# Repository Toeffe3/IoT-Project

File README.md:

# IoT-Project
University Project designing an IoT system

# Setup IDE
### Microchip studio

Following architectures are required:

_Run the `as-installer-*.exe` and select `AVR` and `UC3` (click **Repair**, if you have MCS installed but missing any of the architectures)_

Following extensions are optional:
* `ClangFormat`
* `Git Source Controle Provider`

---

**Integrate with Git trickery**

Open the project the first time by double-clicking the `IoT-Project.atsln` file, if no projects apperes in the Solution Explorer, you have to manually add them by left-clicking the Solution -> Add -> Existing Project -> Navigate to either one of the `*.ccproj` files, and repeat for the other.

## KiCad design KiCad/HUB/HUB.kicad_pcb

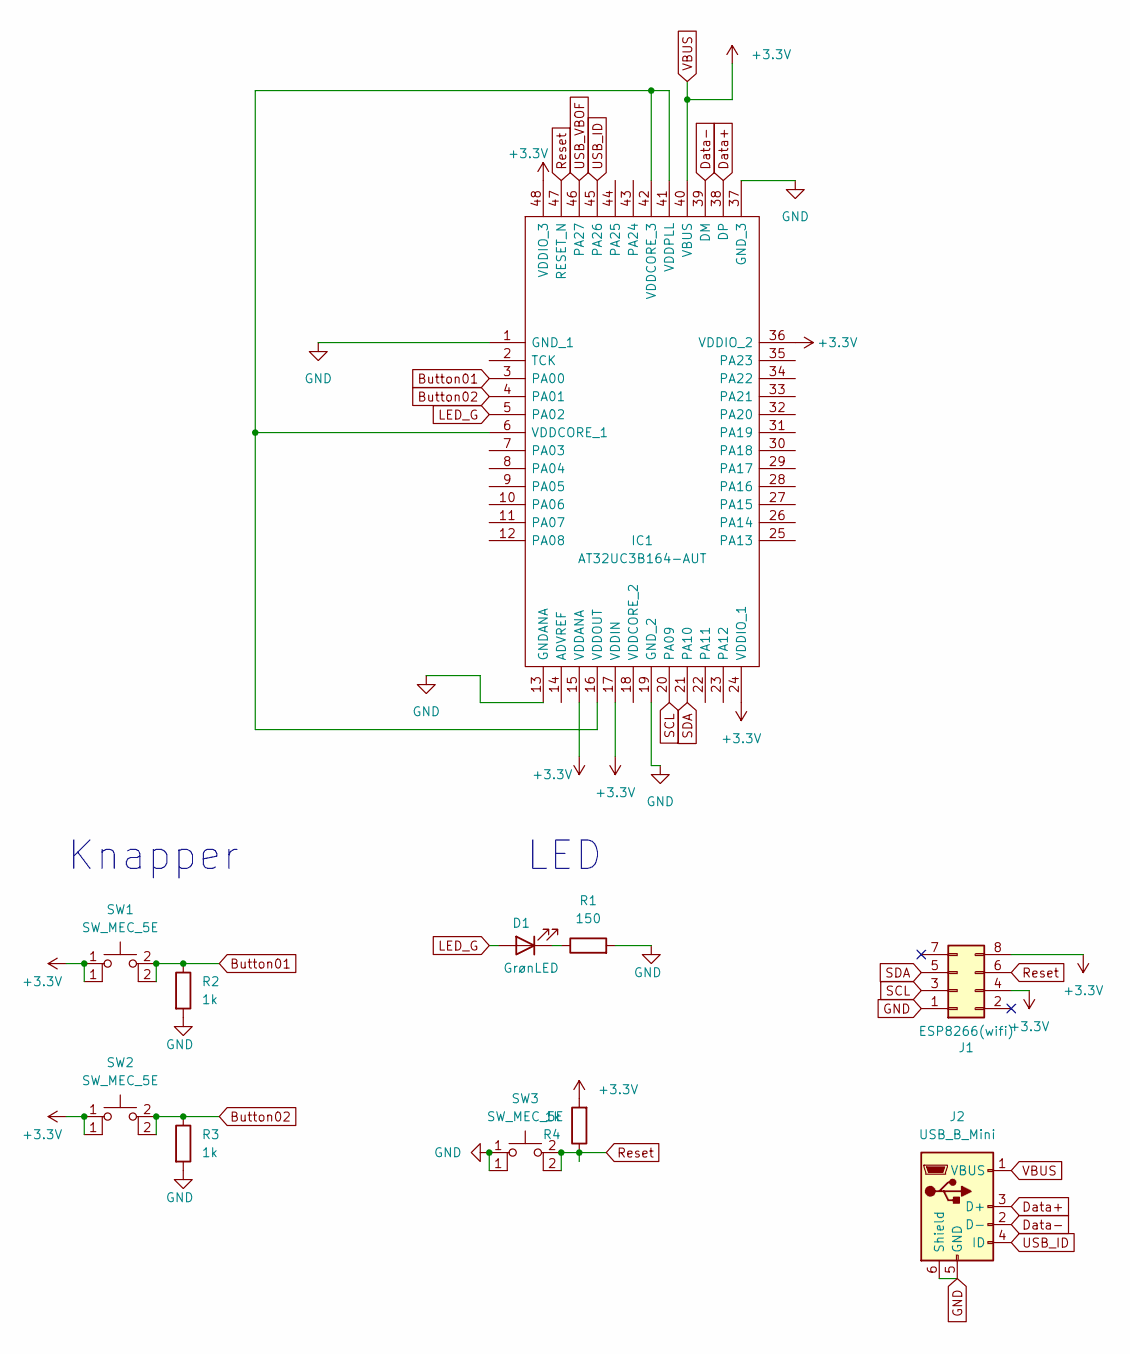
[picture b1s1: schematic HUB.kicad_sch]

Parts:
D1: GrønLED; LED_D3.0mm_FlatTop
IC1: AT32UC3B164-AUT; QFP50P900X900X120-48N; Mouser Part Number 556-AT32UC3B164-AUT
J1: ESP8266(wifi); PinSocket_2x04_P2.54mm_Vertical
J2: USB_B_Mini; USB_Mini-B_Lumberg_2486_01_Horizontal
R1: 150; R_Axial_DIN0309_L9.0mm_D3.2mm_P12.70mm_Horizontal
R2, R3, R4: 1k; R_Axial_DIN0309_L9.0mm_D3.2mm_P12.70mm_Horizontal
SW1, SW2, SW3: SW_MEC_5E; SW_PUSH_6mm_H4.3mm

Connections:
Button01: IC1.3 (PA00), R2.1, SW1.2 (A)
Button02: IC1.4 (PA01), R3.1, SW2.2 (A)
Data+: IC1.38 (DP), J2.3 (D+)
Data-: IC1.39 (DM), J2.2 (D-)
GND: IC1.1 (GND_1), IC1.13 (GNDANA), IC1.19 (GND_2), IC1.37 (GND_3), J1.1, J2.5 (GND), J2.6 (Shield), R1.2, R2.2, R3.2, SW3.1
LED_G: D1.2 (A), IC1.5 (PA02)
unnamed: D1.1 (K), R1.1
unnamed: IC1.6 (VDDCORE_1), IC1.16 (VDDOUT), IC1.41 (VDDPLL), IC1.42 (VDDCORE_3)
Reset: IC1.47 (RESET_N), J1.6, R4.1, SW3.2 (A)
SCL: IC1.20 (PA09), J1.3
SDA: IC1.21 (PA10), J1.5
USB_ID: IC1.45 (PA26), J2.4 (ID)
USB_VBOF: IC1.46 (PA27)
VBUS: IC1.15 (VDDANA), IC1.17 (VDDIN), IC1.24 (VDDIO_1), IC1.36 (VDDIO_2), IC1.40 (VBUS), IC1.48 (VDDIO_3), J1.4, J1.8, J2.1 (VBUS), R4.2, SW1.1, SW2.1

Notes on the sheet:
LED
Knapper

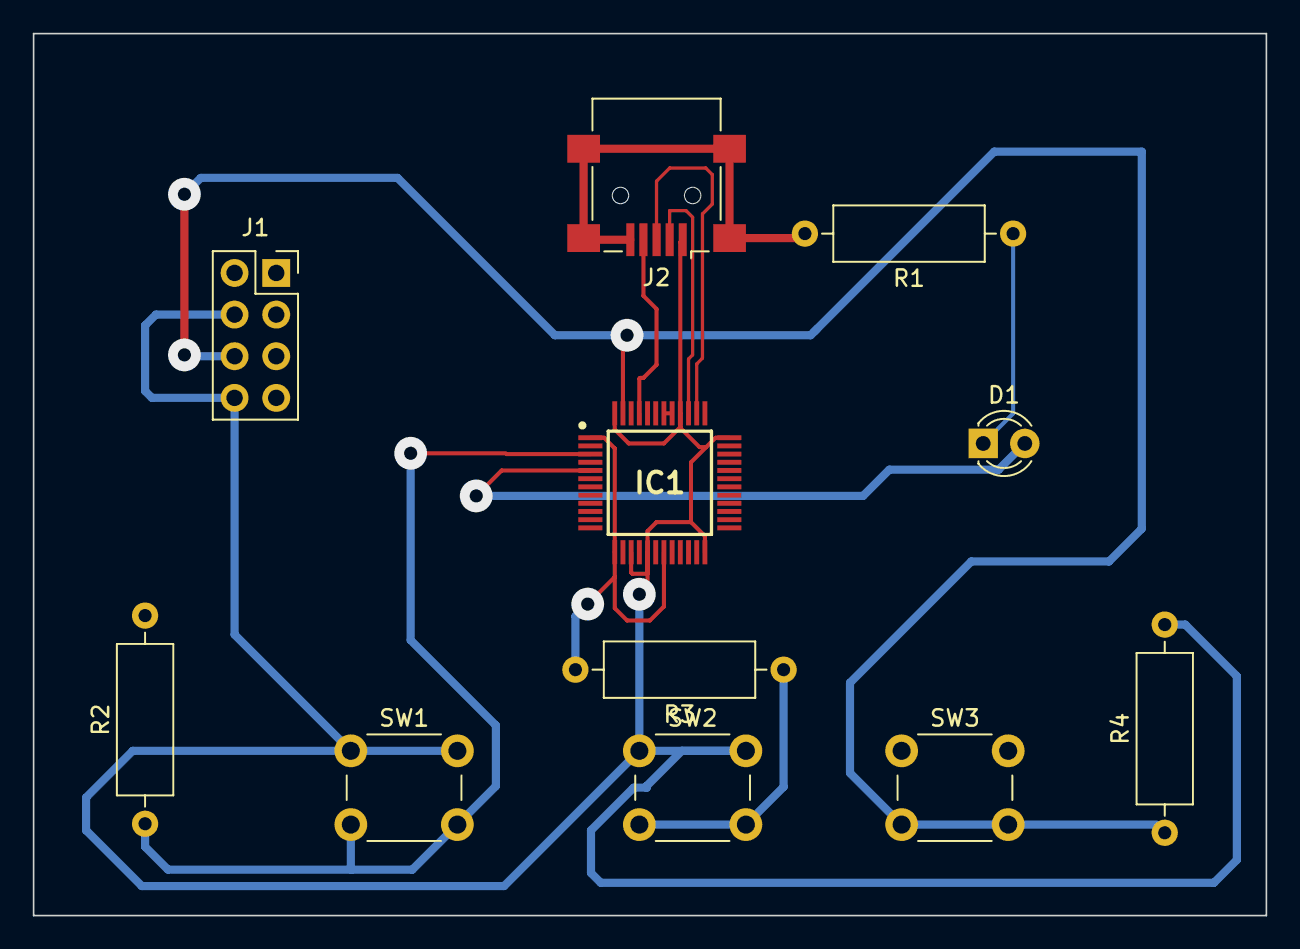
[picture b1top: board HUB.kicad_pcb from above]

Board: 2 copper layers, 75.2 x 53.8 mm, 11 parts (0 on the bottom side), 13 nets.

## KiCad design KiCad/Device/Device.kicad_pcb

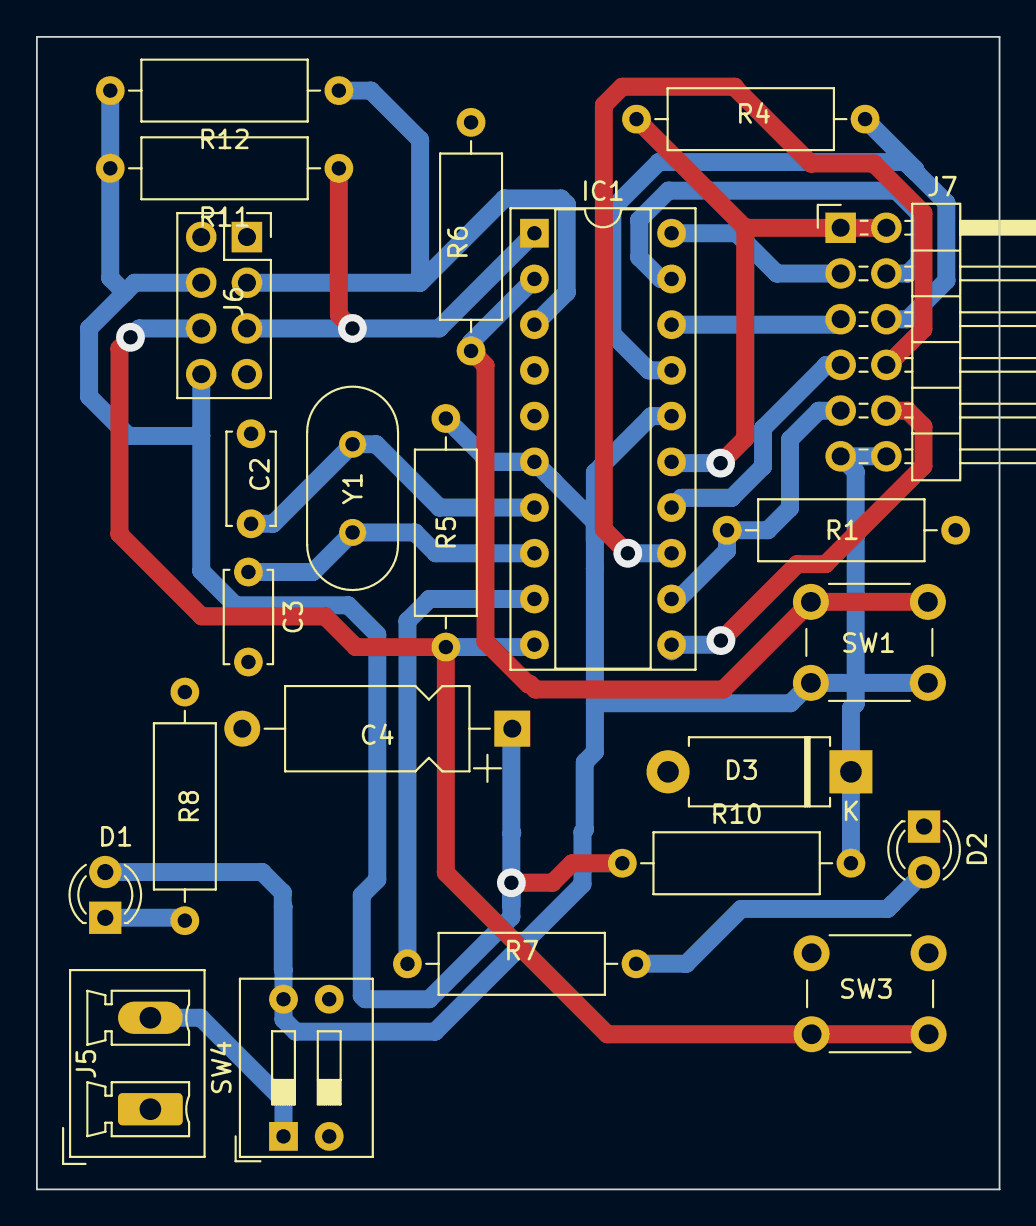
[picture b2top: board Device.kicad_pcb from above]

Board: 2 copper layers, 53.5 x 64.0 mm, 23 parts (0 on the bottom side), 21 nets.

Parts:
C2, C3: 20pF; C_Disc_D5.0mm_W2.5mm_P5.00mm
C4: 100pF; CP_Axial_L10.0mm_D4.5mm_P15.00mm_Horizontal
D1: RødLED; LED_D3.0mm_FlatTop
D2: GrønLED; LED_D3.0mm_FlatTop
D3: BZX79C3V3; D_DO-15_P10.16mm_Horizontal
IC1: ATTINY167-XUR; DIP-20_W7.62mm_Socket
J5: VCC; PhoenixContact_MCV_1,5_2-G-5.08_1x02_P5.08mm_Vertical
J6: ESP8266(wifi); PinSocket_2x04_P2.54mm_Vertical
J7: Conn_02x06_Odd_Even; PinHeader_2x06_P2.54mm_Horizontal
R1: 2k; R_Axial_DIN0309_L9.0mm_D3.2mm_P12.70mm_Horizontal
R4: 100k; R_Axial_DIN0309_L9.0mm_D3.2mm_P12.70mm_Horizontal
R5, R6: 1k; R_Axial_DIN0309_L9.0mm_D3.2mm_P12.70mm_Horizontal
R7, R8: 200; R_Axial_DIN0309_L9.0mm_D3.2mm_P12.70mm_Horizontal
R10: 15; R_Axial_DIN0309_L9.0mm_D3.2mm_P12.70mm_Horizontal
R11, R12: 4.7k; R_Axial_DIN0309_L9.0mm_D3.2mm_P12.70mm_Horizontal
SW1, SW3: SW_MEC_5E; SW_PUSH_6mm_H4.3mm
SW4: SW_DIP_x02; SW_DIP_SPSTx02_Slide_9.78x7.26mm_W7.62mm_P2.54mm
Y1: Crystal; Crystal_HC18-U_Vertical

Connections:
+3V3: C4.1, J6.4, J6.8, R10.1, R11.2, R12.2
+5V: D1.2 (A), D3.1 (K), IC1.6 (VCC), IC1.16 (AVCC), J7.11, J7.12, R5.2, R10.2, SW1.1, SW4.4
Button01: IC1.2 (PB1/DO/OC1BU/PCINT9), R6.1, SW1.2 (A)
DHT11: IC1.20 (PA0/RXLIN/RXD/ADC0/PCINT0), J7.3
GND: C2.2, C3.2, C4.2, D2.1 (K), D3.2 (A), IC1.5 (GND), IC1.15 (AGND), J5.1, J6.1, J7.1, J7.2, R1.2, R4.2, R6.2, R8.2, SW3.1
LED_G: IC1.9 (PB6/INT0/OC1AX/ADC9/PCINT14), R7.1
MIC: IC1.11 (PA7/AREF/XREF/AIN1ADC7/PCINT7), J7.10
unnamed: D1.1 (K), R8.1
unnamed: D2.2 (A), R7.2
unnamed: J5.2, SW4.1
OPTISK: IC1.17 (PA3/INT1/ISRC/ADC3/PCINT3), J7.6, R4.1
PHOTRAN: IC1.12 (PA6/~SS/AIN0/ADC6/PCINT6), J7.9, R1.1
Reset: IC1.10 (PB7/DW/~RESET/OC1BX/ADC10/PCINT15), J6.6, R5.1, SW3.2 (A)
SCL: IC1.3 (PB2/SCL/USCK/OC1AV/PCINT10), J6.3, R12.1
SDA: IC1.1 (PB0/SDA/DI/OCR1AU/PCINT8), J6.5, R11.1
UP1: IC1.19 (PA1/TXLIN/TXD/ADC1/PCINT1), J7.4
UP2: IC1.18 (PA2/MISO/DO/OC0A/ADC2/PCINT2), J7.5
UP4: IC1.14 (PA4/MOSI/SDA/DI/ICP1/ADC4/PCINT4), J7.7
UP5: IC1.13 (PA5/SCK/SCL/USCK/T1/ADC5/PCINT5), J7.8
XTAL1: C2.1, IC1.7 (PB4/CLKI/XTAL1/OC1AW/PCINT12), Y1.1
XTAL2: C3.1, IC1.8 (PB5/CLKO/XTAL2/OC1BW/ADC8/PCINT13), Y1.2

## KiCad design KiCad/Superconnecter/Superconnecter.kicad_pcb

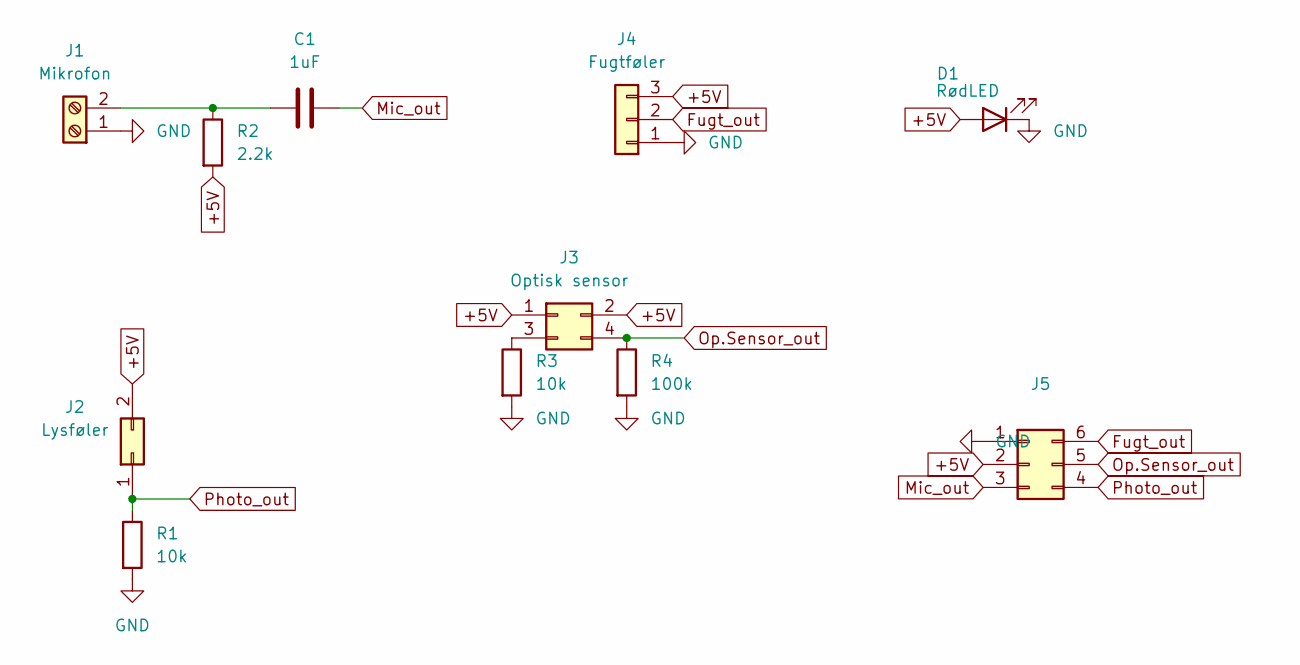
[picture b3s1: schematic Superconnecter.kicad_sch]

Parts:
C1: 1uF; C_Disc_D5.0mm_W2.5mm_P5.00mm
D1: RødLED; LED_D3.0mm_FlatTop
J1: Mikrofon; PhoenixContact_MCV_1,5_2-G-5.08_1x02_P5.08mm_Vertical
J2: Lysføler; PinSocket_2x01_P2.54mm_Vertical
J3: Optisk sensor; PinSocket_2x02_P2.54mm_Vertical
J4: Fugtføler; PinSocket_1x03_P2.54mm_Vertical
J5: (no value)
R1, R3: 10k; R_Axial_DIN0309_L9.0mm_D3.2mm_P12.70mm_Horizontal
R2: 2.2k; R_Axial_DIN0309_L9.0mm_D3.2mm_P12.70mm_Horizontal
R4: 100k; R_Axial_DIN0309_L9.0mm_D3.2mm_P12.70mm_Horizontal

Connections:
+5V: D1.2 (A), J2.2, J3.1, J3.2, J4.3, J5.2, R2.2
Fugt_out: J4.2, J5.6
GND: D1.1 (K), J1.1, J4.1, J5.1, R1.2, R3.2, R4.2
Mic_out: C1.2, J5.3
unnamed: C1.1, J1.2, R2.1
unnamed: J3.3, R3.1
Op.Sensor_out: J3.4, J5.5, R4.1
Photo_out: J2.1, J5.4, R1.1

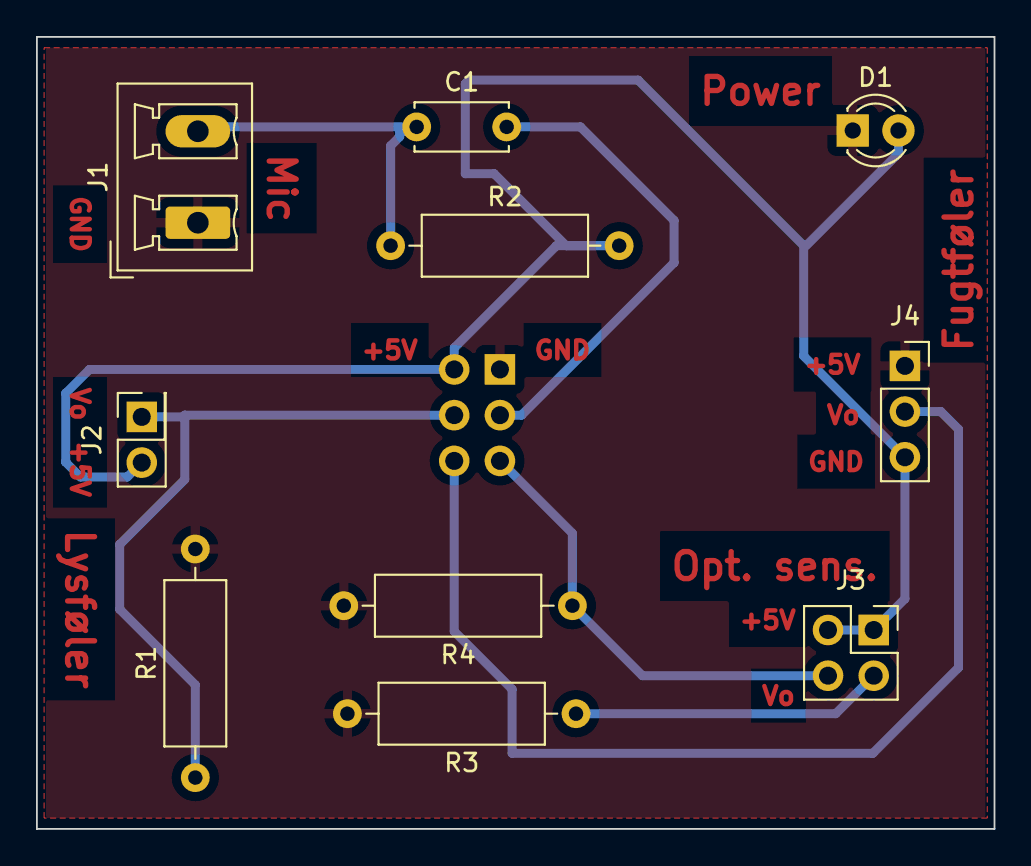
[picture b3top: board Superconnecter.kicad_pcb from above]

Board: 2 copper layers, 53.2 x 44.0 mm, 11 parts (1 on the bottom side), 8 nets.

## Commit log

2022-03-08 Solution setup
2022-03-08 Setup
2022-03-08 Fix project
2022-03-09 Header setup
2022-03-10 apply clang-format
2022-03-10 test
2022-03-10 🎨 Formattede code
2022-03-10 Fix formatter
2022-03-10 Target all c and cpp files
2022-03-10 Format final fix
2022-03-11 Fix .clang-format Update README.md
2022-03-11 Create CODEOWNERS
2022-03-29 Tidsplan
2022-03-29 Added Projectplan.xlsx
2022-03-30 Init kicad
2022-03-30 Tilføjelse til Device
2022-03-30 device tilføjelse
2022-03-30 RTC pretest
2022-03-30 Device tilføjelser
2022-03-30 I2C pretest
2022-04-04 kicad device fodlister
2022-04-05 spreadout board to device
2022-04-05 IO test
2022-04-05 Opdatering af device kicad
2022-04-05 Minor fixes
2022-04-05 fix ic
2022-04-05 Opdatering af switches
2022-04-05 GPIO WIP
    ikke helt færdig
2022-04-05 Fungerende_men_grimt_print
2022-04-05 Superconnecter
2022-04-05 Kompakt design
2022-04-05 GPIO
2022-04-05 save
2022-04-06 ændringer
2022-04-06 Ny_connecter
2022-04-06 Fix til RTC & GPIO
2022-04-06 flip sides
2022-04-06 Change track width
2022-04-06 HUB_Schematic_done
2022-04-07 AVRDUDE configuration for device
2022-04-07 Fix device
2022-04-07 Update .clang-format
2022-04-07 Næsten_færdigt_pcb
2022-04-07 get uploading fixed
2022-04-08 fix build.sh
2022-04-12 Kode start
2022-04-12 Debug
2022-04-12 kicad
2022-04-20 Device (post test)
2022-04-27 LDR (pre-test)
2022-04-27 Opdateret pcb
2022-04-27 LDR (post-test)
2022-05-12 Reworked
2022-05-12 Update fp-info-cache
2022-05-12 ticks
2022-05-12 Opdateret connecter 5v
2022-05-12 fix??
2022-05-12 Output (pre-test)
2022-05-14 power pretest
2022-05-17 SSD (redefine)
2022-05-18 com pretest
2022-05-18 temperatur (doesn't work)
2022-05-18 com num
2022-05-18 LDR com (post-test)
2022-05-19 Tiva_hub
    som kom det
2022-05-19 File structure
2022-05-21 COM done and tested
2022-05-22 Final coding
2022-05-23 fix folders
2022-05-23 fix frt10 folder
2022-05-23 fix FRT10 folder
    Needed to remove comit and add again, mv did not detect it
2022-05-23 Block comments
2022-05-23 fix encoding
2022-05-23 fix file names
2022-05-23 fix filenames 2
2022-05-23 fix filenames 3
